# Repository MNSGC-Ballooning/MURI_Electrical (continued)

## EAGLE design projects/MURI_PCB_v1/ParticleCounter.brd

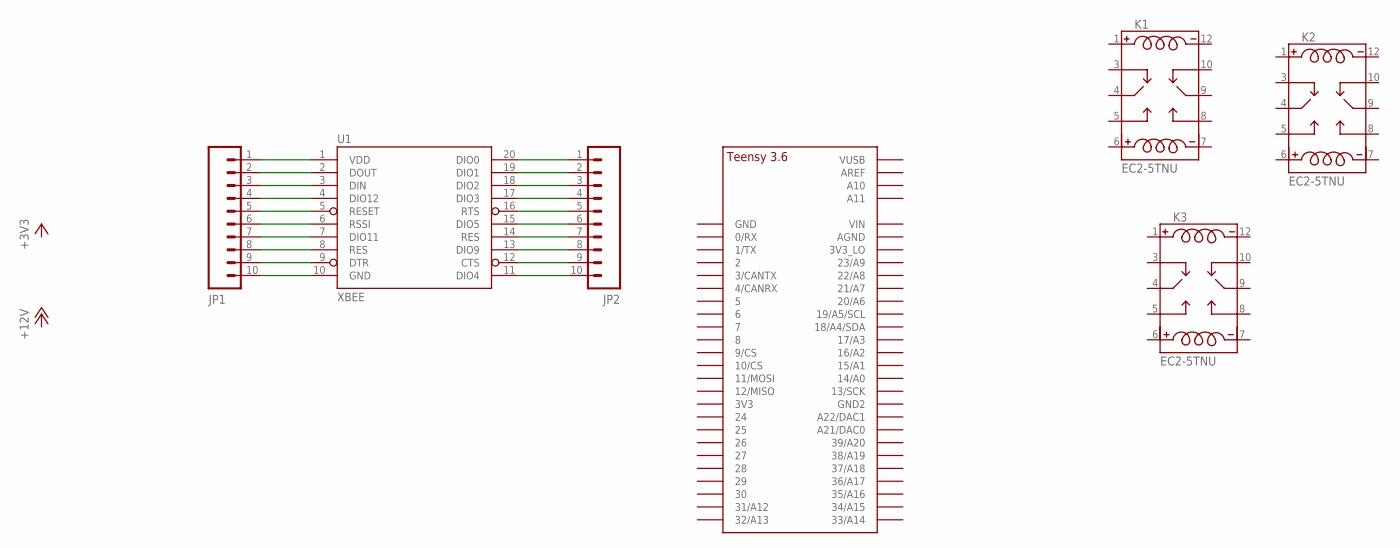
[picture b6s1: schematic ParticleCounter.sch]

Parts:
JP1, JP2: M100.1; 1X10
K1, K2, K3: EC2-5TNU; RELAY_EC2-5TNU
U1: XBEE; XBEE-1
U$1: TEENSY_3.5/3.6_BASIC

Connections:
unnamed: JP1.5, U1.5 (RESET)
unnamed: JP1.1, U1.1 (VDD)
unnamed: JP1.2, U1.2 (DOUT)
unnamed: JP1.3, U1.3 (DIN)
unnamed: JP1.4, U1.4 (DIO12)
unnamed: JP1.6, U1.6 (RSSI)
unnamed: JP1.7, U1.7 (DIO11)
unnamed: JP1.8, U1.8 (RES)
unnamed: JP1.9, U1.9 (DTR)
unnamed: JP1.10, U1.10 (GND)
unnamed: JP2.10, U1.11 (DIO4)
unnamed: JP2.9, U1.12 (CTS)
unnamed: JP2.8, U1.13 (DIO9)
unnamed: JP2.7, U1.14 (RES)
unnamed: JP2.6, U1.15 (DIO5)
unnamed: JP2.5, U1.16 (RTS)
unnamed: JP2.4, U1.17 (DIO3)
unnamed: JP2.3, U1.18 (DIO2)
unnamed: JP2.2, U1.19 (DIO1)
unnamed: JP2.1, U1.20 (DIO0)

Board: 2 copper layers, 7 parts (0 on the bottom side), 20 nets, no tracks yet.

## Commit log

2020-05-30 Frequently used Eagle libraries
2020-05-30 Eagle updated PCB projects
2020-06-03 First Iteration Resistor Cutaway
2020-06-03 Updated first iteration of resistor cutaway PCB
2020-06-03 CAM output resistor cutaway PCB
2020-06-22 Second iteration of the resistor cutaway board/schematic
2020-06-22 Second iteration of resistor cutaway PCB
2020-06-24 Second iteration of the COMPASS PCB
2020-08-11 COMPASS V2 CAM Outputs
2020-08-11 Resistor Cutaway V3 PCB
2020-08-29 Third Iteration of Compass Board
    Added variable voltage regulator
2020-11-30 Updated Compass Board to fit on the side edge of the N3 particle counter
2021-01-04 First iteration of venting PCB
2021-02-16 Final iterations of Cutter and Compass boards
2021-06-08 Second iteration of venting PCB
